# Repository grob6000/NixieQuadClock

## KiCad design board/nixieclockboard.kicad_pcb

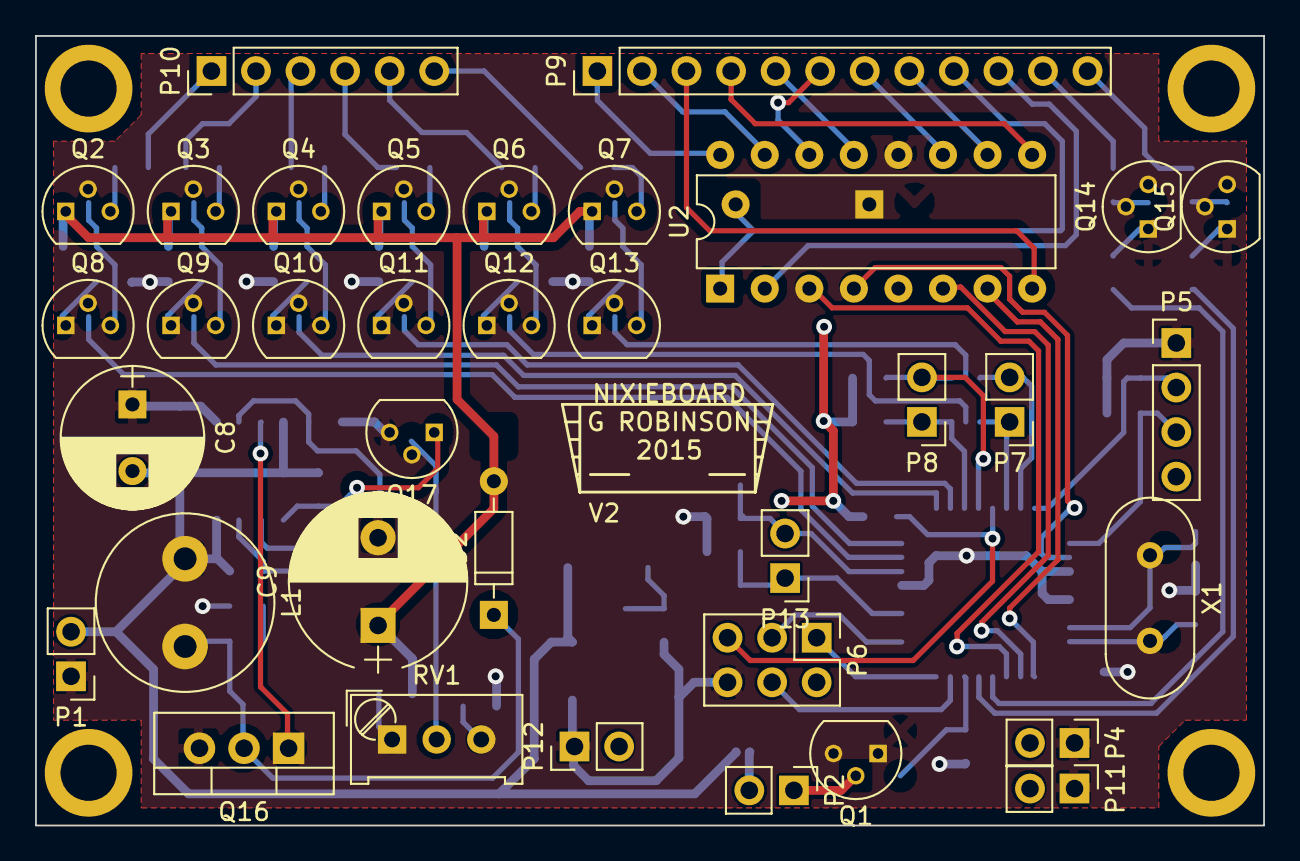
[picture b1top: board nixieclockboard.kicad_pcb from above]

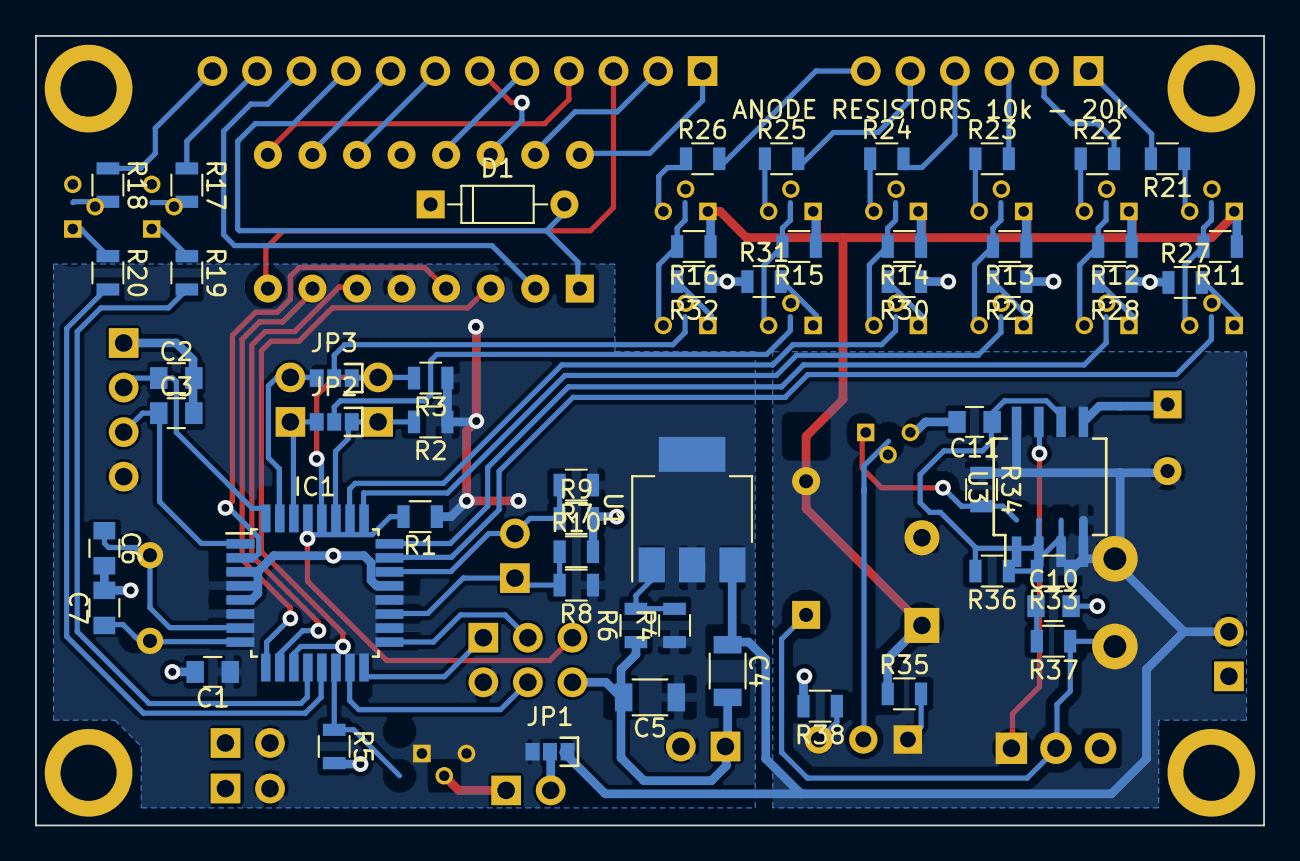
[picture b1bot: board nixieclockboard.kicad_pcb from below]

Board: 2 copper layers, 70.0 x 45.0 mm, 94 parts (54 on the bottom side), 81 nets.

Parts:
C1, C2, C3: 0u1; C_0805
C4, C5: 10u; C_1206
C6, C7: 22p; C_0805
C8: 330u; CP_Radial_D8.0mm_P3.80mm
C9: 10u; CP_Radial_D10.0mm_P5.00mm
C10: 100p; C_0805
C11: 2n2; C_0805
D1: 30V; D_DO-35_SOD27_P7.62mm_Horizontal
D2: UF4004; D_DO-35_SOD27_P7.62mm_Horizontal
IC1: ATMEGA328P-A; TQFP-32_7x7mm_Pitch0.8mm
JP1: VBUZZ; JUMPER_SMD_3
JP2: S4/SDA; JUMPER_SMD_3
JP3: S5/SCL; JUMPER_SMD_3
L1: 100uH; L_Radial_D10.0mm_P5.00mm_Fastron_07M
P1: PWR; Pin_Header_Straight_1x02_Pitch2.54mm
P2: BUZZ; Pin_Header_Straight_1x02_Pitch2.54mm
P4, P11, P12: 5V; Pin_Header_Straight_1x02_Pitch2.54mm
P5: BTN; Pin_Header_Straight_1x04_Pitch2.54mm
P6: ISP; Pin_Header_Straight_2x03_Pitch2.54mm
P7: SERIAL; Pin_Header_Straight_1x02_Pitch2.54mm
P8: I2C; Pin_Header_Straight_1x02_Pitch2.54mm
P9: D0; Pin_Header_Straight_1x12_Pitch2.54mm
P10: ANODE; Pin_Header_Straight_1x06_Pitch2.54mm
P13: ADC; Pin_Header_Straight_1x02_Pitch2.54mm
Q1: 2N7000; TO-92_Molded_Narrow
Q2, Q3, Q4, Q5, Q6, Q7: MPSA92; TO-92_Molded_Narrow
Q8, Q9, Q10, Q11, Q12, Q13, Q14, Q15: MPSA42; TO-92_Molded_Narrow
Q16: IRF740; TO-220_Vertical
Q17: BC547; TO-92_Molded_Narrow
R1: 4k7; R_0805
R2, R3, R5, R17, R18, R27, R28, R29, R30, R31, R32, R36: 10k; R_0805
R4: 120; R_0805
R6: 360; R_0805
R7, R8, R9, R10, R21, R22, R23, R24, R25, R26: R; R_0805
R11, R12, R13, R14, R15, R16, R19, R20: 100k; R_0805
R33: 1k; R_0805
R34: 56k; R_0805
R35: 220k; R_0805
R37: 2k2; R_0805
R38: 470; R_0805
RV1: 1k; Potentiometer_Trimmer_Bourns_PV36W
SCREW_M3, SCREW_M3#2, SCREW_M3#3, SCREW_M3#4: VAL**; SCREW_M3
U1: LM1117; SOT-223-3Lead_TabPin2
U2: K155ID1; DIP-16_W7.62mm
U3: 555; SO-8_5.3x6.2mm_Pitch1.27mm
X1: 18.432MHz; Crystal_HC49-4H_Vertical

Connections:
/A0: P10.1, R21.2
/A1: P10.2, R22.2
/A2: P10.3, R23.2
/A3: P10.4, R24.2
/A4: P10.5, R25.2
/A5: P10.6, R26.2
/ADC6: IC1.19, P13.1, R8.2, R10.1
/ADC7: IC1.22, P13.2, R7.2, R9.1
/ADJ: R4.2, R6.2, U1.1
/AE0: Q2.3, R21.1
/AE1: Q3.3, R22.1
/AE2: Q4.3, R23.1
/AE3: Q5.3, R24.1
/AE4: Q6.3, R25.1
/AE5: Q7.3, R26.1
/BALARM: C2.1, IC1.32, P5.2
/BIT0: IC1.11, U2.3
/BIT1: IC1.10, U2.6
/BIT2: IC1.9, U2.7
/BIT3: IC1.2, U2.4
/BUZ+: JP1.2, P2.2
/BUZZ: IC1.14, R5.1
/BZONE: C3.1, IC1.1, P5.3
/C0: P9.1, U2.16
/C1: P9.2, U2.15
/C2: P9.3, U2.8
/C3: P9.4, U2.9
/C4: P9.5, U2.13
/C5: P9.6, U2.14
/C6: P9.7, U2.11
/C7: P9.8, U2.10
/C8: D1.2, P9.9, U2.1
/C9: P9.10, U2.2
/CL: P9.11, R17.1
/CLB: Q14.2, R19.1
/CLC: Q14.3, R17.2
/CR: P9.12, R18.1
/CRB: Q15.2, R20.1
/CRC: Q15.3, R18.2
/HVSupply/DIS: R33.2, R36.1, U3.7
/HVSupply/FB: Q17.2, RV1.2
/HVSupply/NPNC: Q17.3, R34.2, U3.5
/HVSupply/RCFIL: C10.1, R37.2
/HVSupply/RVN: R38.1, RV1.3
/HVSupply/RVP: R35.2, RV1.1
/HVSupply/TRG: C11.1, R36.2, U3.2, U3.6
/HVSupply/VPUMP: D2.1, L1.2, R37.1
/LCOMMA: IC1.12, R19.2
/MISO: IC1.16, P6.1
/MOSI: IC1.15, P6.4
/NPNB0: Q8.1, R27.2
/NPNB1: Q9.1, R28.2
/NPNB2: Q10.1, R29.2
/NPNB3: Q11.1, R30.2
/NPNB4: Q12.1, R31.2
/NPNB5: Q13.1, R32.2
/PNPB0: Q2.2, Q8.3, R11.2
/PNPB1: Q3.2, Q9.3, R12.2
/PNPB2: Q4.2, Q10.3, R13.2
/PNPB3: Q5.2, Q11.3, R14.2
/PNPB4: Q6.2, Q12.3, R15.2
/PNPB5: Q7.2, Q13.3, R16.2
/RCOMMA: IC1.13, R20.2
/RESET: IC1.29, P6.5, R1.2
/RXD: IC1.30, JP2.3, P7.1
/S0: IC1.23, Q8.2
/S1: IC1.24, Q9.2
/S2: IC1.25, Q10.2
/S3: IC1.26, Q11.2
/S4: JP2.2, Q12.2
/S5: JP3.2, Q13.2
/SCK: IC1.17, P6.3
/SCL: IC1.28, JP3.1, P8.2, R3.2
/SDA: IC1.27, JP2.1, P8.1, R2.2
/TXD: IC1.31, JP3.3, P7.2
/VCC: C1.1, C5.1, IC1.4, IC1.6, IC1.18, IC1.20, JP1.3, P4.2, P5.4, P6.2, P11.2, P12.2, R1.1, R2.1, R3.1, R4.1, R7.1, R8.1, U1.2, U2.5
/VSUP: C4.1, C8.1, JP1.1, L1.1, P1.2, R33.1, R34.1, U1.3, U3.4, U3.8
/X1: C6.1, IC1.7, X1.1
/X2: C7.1, IC1.8, X1.2
GND: C1.2, C2.2, C3.2, C4.2, C5.2, C6.2, C7.2, C8.2, C9.2, C10.2, C11.2, D1.1, IC1.3, IC1.5, IC1.21, P1.1, P4.1, P5.1, P6.6, P11.1, P12.1, Q14.1, Q15.1, Q17.1, R5.2, R6.1, R9.2, R10.2, R27.1, R28.1, R29.1, R30.1, R31.1, R32.1, R38.2, U2.12, U3.1
HV: C9.1, D2.2, Q2.1, Q3.1, Q4.1, Q5.1, Q6.1, Q7.1, R11.1, R12.1, R13.1, R14.1, R15.1, R16.1, R35.1

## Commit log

2015-01-11 :boom::camel: Added .gitattributes & .gitignore files
2015-01-11 Update gitignore
2015-01-11 Initial Add Board Files
2015-01-11 Initial Add Model Files
2015-01-11 Schematic updates
2015-01-21 Schematic and board creation continued
2015-03-24 Board completed
2015-03-24 Board plot for manufacture
2015-03-24 Model updates continued
2015-05-10 More Board Edits
2015-05-10 Firmware Edits
2015-05-10 Model Edits
2015-05-10 Update gitignore 2
2015-05-10 Testing spreadsheet
2015-05-27 Firmware updates
    Nearly finished... Start proper commits from here.
2015-05-27 Model changes
2015-05-27 Buzzer and alarm implementation
2015-06-01 Fix eeprom storage bug, fix button repeat delay
    * Used uint8_t where uint16_t was required for temp var
    * Did not set repeat mode correctly in all cases
2015-06-02 Replace BUZZER_xx with xx(BUZZ) macros
    For consistency, use of assigned pins.
2015-06-02 Create sound module files
2015-06-02 More sound module
    Still not working!
2015-06-02 Fix #1 - buttons not working during alarm mute
2015-06-02 Now builds!
2015-06-02 Fix some defines in nixieclock.h
2015-06-02 Use pins.h for button checks
2015-06-03 Button check should be low enabled
2015-06-03 Button check should be low enabled 2/2
2015-06-04 Improve pins.h macros
    No longer needs separate definitions for PORTx, DDRx and PINx. Config
    definitions now just letter and bit number.
2015-06-05 Move config to config.h
2021-04-23 Add board design
2021-04-23 SW convert to step files
2021-04-23 Update model
2021-04-23 Firmware project files upgrade to atmel studio 7
2021-04-24 Add features
    * Cogniscent of dates
    * Auto off display function
    * NMEA parsing follows commas (SKM53 pads with an invalid time, but other GPS units provide zero-length fields - this is more robust hopefully)
2021-04-24 Project save
    Build success
2021-04-25 Bugfixes in NMEA parsing
2021-04-25 Make display on boot
2021-04-25 Autooff only overnight
2021-06-14 Autooff turns on by itself in the morning
